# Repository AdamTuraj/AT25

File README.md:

# AT25 - A cooler RC Car

The goal of this project is to build experience for a potential future in motorsports / Formula Student. As a fan of road car racing, I will be designing the aero and suspension car roughly around the LMGT3 regulations.

### Requirements

Below are the goals of this project. The self-imposed regulations I will be following when designing the car:

- Aerodynamic elements that work and are CFD optimized
- Double Wishbone suspension
- AWD with one sensored brushless motors
- Braking with the electric motor
- Mostly made of plastic with the exception of:
  - Gearing in the diffs
  - The electronic parts
  - The wheels
  - Any gaskets that may be required
  - Fasteners
- Remote controlled
- Fits a Lego mini figure in a driver seat

### Journal

I will be recording my day to day work in a journal found [here](https://github.com/AdamTuraj/AT25/blob/main/JOURNAL.md)

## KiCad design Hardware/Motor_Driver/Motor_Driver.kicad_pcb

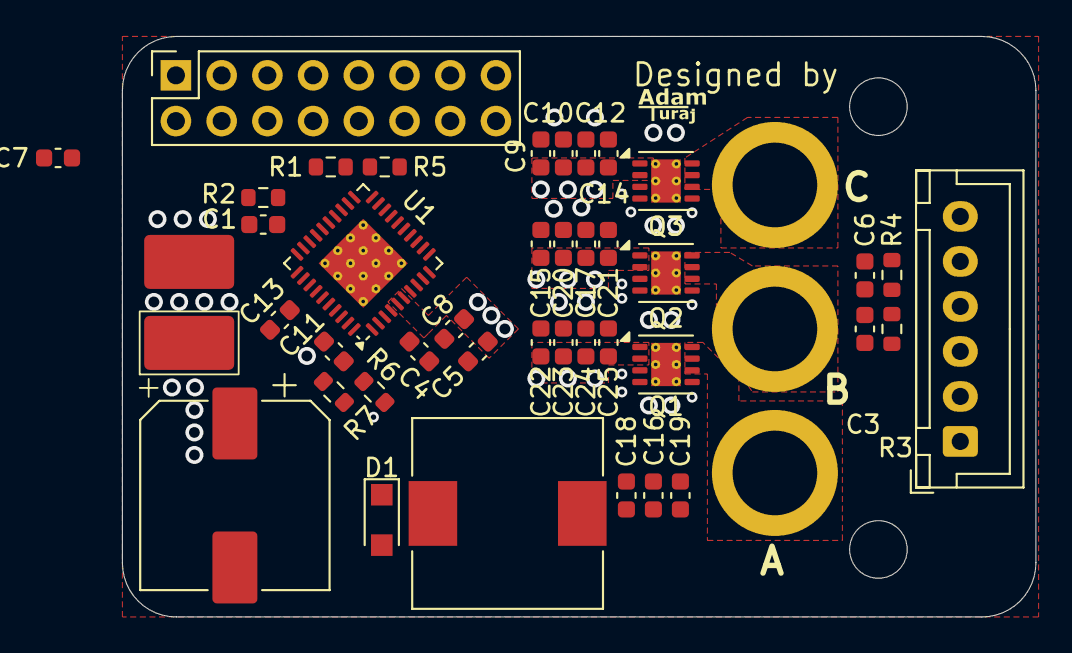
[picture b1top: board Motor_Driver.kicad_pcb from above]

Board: 4 copper layers, 50.8 x 32.2 mm, 42 parts (0 on the bottom side), 38 nets, no tracks yet.

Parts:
C1, C3, C6: 10nF; C_0603_1608Metric
C2: 100uF; CP_Elec_10x10
C4: 47nF; C_0603_1608Metric
C5, C13, C14, C21, C25: 0.1uF; C_0603_1608Metric
C7, C8: 1uF; C_0603_1608Metric
C9, C10, C12, C15, C17, C20, C22, C23, C24: 4.7uF; C_0603_1608Metric
C11: 10uF; C_0603_1608Metric
C16, C18, C19: 1.5uF; C_0603_1608Metric
D1: 340mV@1A; Nexperia_CFP3_SOD-123W
J1: Conn_PWR; SolderWirePad_1x02_SMD_5x10mm
J2: Conn_MB; PinSocket_2x08_P2.54mm_Vertical
J3: Conn_SENSORS; JST_XH_B6B-XH-A_1x06_P2.50mm_Vertical
J4: Conn_MOTOR; Pin_Bullet_D4.7mm
L1: 33uH; L_10.4x10.4_H4.8
Q1, Q2, Q3: CSD87333Q3D; VSON-8-1EP_3x3mm_P0.65mm_EP1.65x2.4mm_ThermalVias
R1, R5, R7: 10k4; R_0603_1608Metric
R2, R3, R4: 100R; R_0603_1608Metric
R6: 57k6; R_0603_1608Metric
U1: DRV8320RS; VQFN-40-1EP_6x6mm_P0.5mm_EP3.5x3.5mm_ThermalVias

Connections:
+3V3: C7.1, R1.2, R5.2, U1.27 (DVDD)
+5V: C16.1, C18.1, C19.1, J2.2, J3.1, L1.2, R6.1
/BRAKE: J2.6, U1.33 (INLC)
/CLK: J2.9, U1.23 (SCLK)
/CS: J2.8, U1.24 (nSCS)
/DIR: J2.5, U1.32 (INHC)
/EN: J2.3, U1.25 (ENABLE)
/FAULT: J2.7, R5.1, U1.20 (nFAULT)
/HALL_A: C1.1, J2.13, R2.1, U1.29 (INLA)
/HALL_B: C3.1, J2.14, R3.1, U1.30 (INHB)
/HALL_C: C6.1, J2.15, R4.1, U1.31 (INLB)
/PWM: J2.4, U1.28 (INHA)
/Phase_A.GH: Q1.3 (T_{G}), U1.7 (GHA)
/Phase_A.GL: Q1.5 (B_{G}), U1.9 (GLA)
/Phase_A.SH: Q1.4 (T_{GR}), U1.8 (SHA)
/Phase_B.GH: Q2.3 (T_{G}), U1.14 (GHB)
/Phase_B.GL: Q2.5 (B_{G}), U1.12 (GLB)
/Phase_B.SH: Q2.4 (T_{GR}), U1.13 (SHB)
/Phase_C.GH: Q3.3 (T_{G}), U1.15 (GHC)
/Phase_C.GL: Q3.5 (B_{G}), U1.17 (GLC)
/Phase_C.SH: Q3.4 (T_{GR}), U1.16 (SHC)
/SDI: J2.10, U1.22 (SDI)
/SDO: J2.11, R1.1, U1.21 (SDO)
/TEMP: J2.12, J3.6
GND: C1.2, C2.2, C3.2, C5.2, C6.2, C7.2, C9.2, C10.2, C11.2, C12.2, C14.2, C15.2, C16.2, C17.2, C18.2, C19.2, C20.2, C21.2, C22.2, C23.2, C24.2, C25.2, D1.2 (A), J1.2, J2.16, J3.5, Q1.9 (P_{GND}), Q2.9 (P_{GND}), Q3.9 (P_{GND}), R7.2, U1.1 (PGND), U1.10 (SLA), U1.11 (SLB), U1.18 (SLC), U1.19 (GND), U1.26 (AGND), U1.34 (BGND), U1.41 (PAD)
unnamed: C13.2, D1.1 (K), L1.1, U1.36 (SW)
unnamed: J3.2, R2.2
unnamed: J3.3, R3.2
unnamed: J3.4, R4.2
unnamed: J4.1, Q1.6 (V_{SW}), Q1.7 (V_{SW}), Q1.8 (V_{SW})
unnamed: J4.2, Q2.6 (V_{SW}), Q2.7 (V_{SW}), Q2.8 (V_{SW})
unnamed: J4.3, Q3.6 (V_{SW}), Q3.7 (V_{SW}), Q3.8 (V_{SW})
unnamed: C13.1, U1.35 (CB)
unnamed: C4.1, U1.3 (CPH)
unnamed: C4.2, U1.2 (CPL)
unnamed: R6.2, R7.1, U1.40 (FB)
unnamed: C8.2, U1.4 (VCP)
VM: C2.1, C5.1, C8.1, C9.1, C10.1, C11.1, C12.1, C14.1, C15.1, C17.1, C20.1, C21.1, C22.1, C23.1, C24.1, C25.1, J1.1, J2.1, Q1.1 (V_{IN}), Q1.2 (V_{IN}), Q2.1 (V_{IN}), Q2.2 (V_{IN}), Q3.1 (V_{IN}), Q3.2 (V_{IN}), U1.5 (VM), U1.6 (VDRAIN), U1.38 (VIN)

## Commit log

2025-06-20 Day 1
2025-06-20 Adjust goals
2025-06-20 Day 2 + Changes to requirements
2025-06-21 Format changes to BOM
2025-06-22 Add day 3 and schematic for the motor driver
2025-06-23 Day 4
2025-06-30 Day 5 - Finish motor driver PCB
2025-06-30 Fix created_at date
2025-07-03 Day 6
